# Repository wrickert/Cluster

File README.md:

# Cluster
Replacment cluster for GL1200 motorcycle. This is an early prototype to test how signals work. Main uC is Stm32f411re, will be running freertos. <br>

# Updates
1April - ordered v1 prototype<br>

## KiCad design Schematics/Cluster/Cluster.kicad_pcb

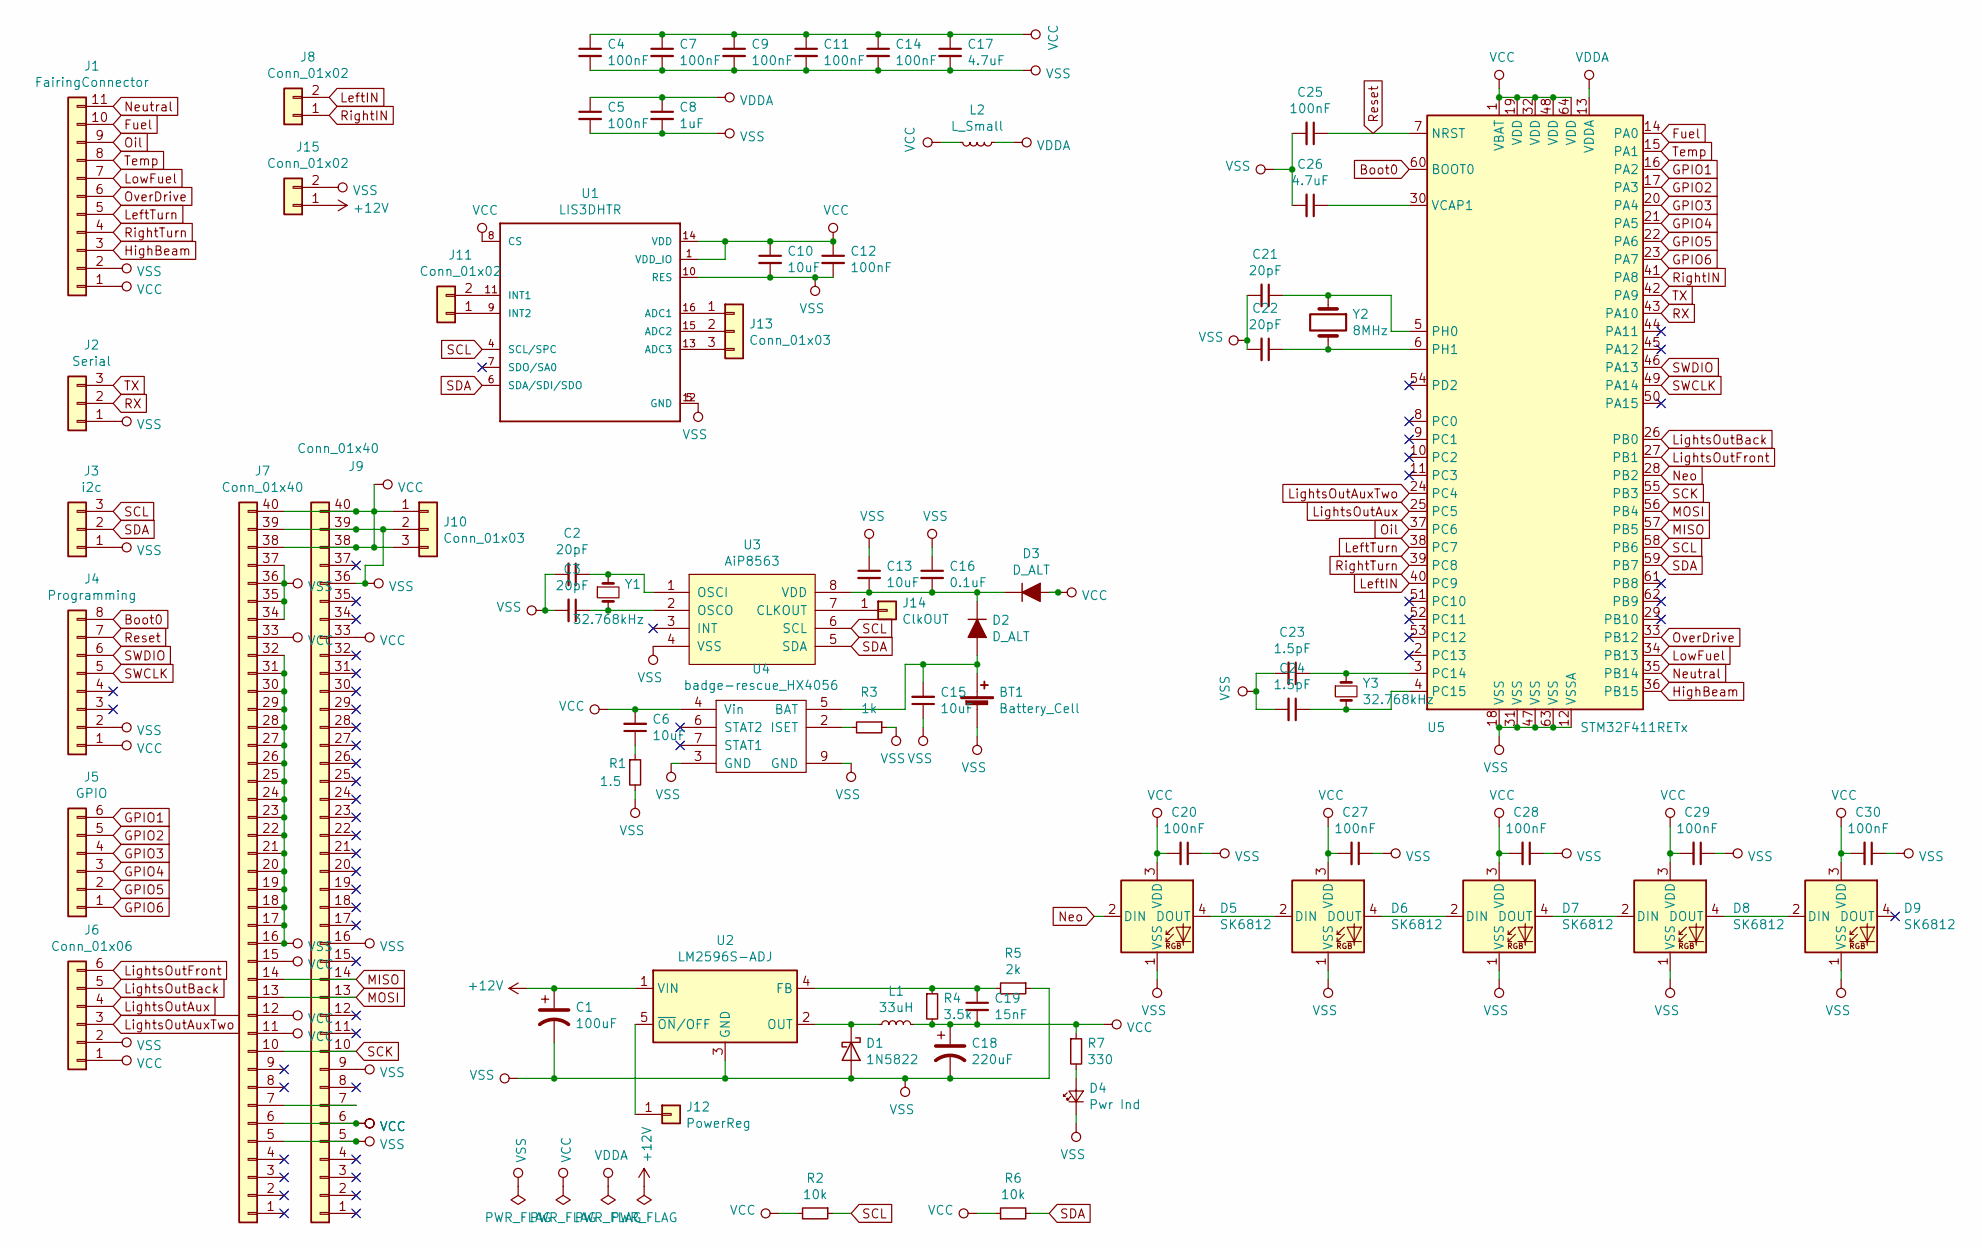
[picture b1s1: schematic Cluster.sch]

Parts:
BT1: Battery_Cell; Keystone_3008_1x2450-CoinCell
C1: 100uF; CP_Elec_8x10.5
C2, C3, C21, C22: 20pF; C_0805_2012Metric
C4, C5, C7, C9, C11, C12, C14, C20, C25, C27, C28, C29, C30: 100nF; C_0805_2012Metric
C6, C10, C13, C15: 10uF; C_0805_2012Metric
C8: 1uF; C_0805_2012Metric
C16: 0.1uF; C_0805_2012Metric
C17, C26: 4.7uF; C_0805_2012Metric
C18: 220uF; CP_Elec_8x10.5
C19: 15nF; C_0805_2012Metric
C23, C24: 1.5pF; C_0805_2012Metric
D1: 1N5822; D_SMA
D2, D3: D_ALT; D_0603
D4: Pwr Ind; LED_0603_1608Metric
D5, D6, D7, D8, D9: SK6812; LED_WS2812B-PLCC4
J1: FairingConnector; TerminalBlock_RND_205-00021_1x11_P5.00mm_Horizontal
J2: Serial; PinHeader_1x03_P2.54mm_Vertical
J3: i2c; PinHeader_1x03_P2.54mm_Vertical
J4: Programming; PinHeader_1x08_P2.54mm_Vertical
J5: GPIO; PinHeader_1x06_P2.54mm_Vertical
J6: Conn_01x06; PinHeader_1x06_P2.54mm_Vertical
J7: Conn_01x40; XF2M-4015
J8: Conn_01x02; TerminalBlock_RND_205-00001_Pitch5.00mm
J9: Conn_01x40; PinHeader_1x40_P1.00mm_Vertical
J10, J13: Conn_01x03; PinHeader_1x03_P2.54mm_Vertical
J11: Conn_01x02; PinHeader_1x02_P2.54mm_Vertical
J12: PowerReg; PinHeader_1x01_P2.54mm_Vertical
J14: ClkOUT; PinHeader_1x01_P2.54mm_Vertical
J15: Conn_01x02; TerminalBlock_RND_205-00012_1x02_P5.00mm_Horizontal
L1: 33uH; L_6.3x6.3_H3
L2: L_Small; L_0603_1608Metric
R1: 1.5; R_0805
R2, R6: 10k; R_0805
R3: 1k; R_0805
R4: 3.5k; R_0805
R5: 2k; R_0805
R7: 330; R_0603_1608Metric
U1: LIS3DHTR; LGA16R50P5X3_300X300X100N
U2: LM2596S-ADJ; TO-263-5_TabPin3
U3: AiP8563; MSOP-8_3x3mm_Pitch0.65mm
U4: badge-rescue_HX4056; HX4056
U5: STM32F411RETx; LQFP-64_10x10mm_Pitch0.5mm
Y1: 32.768kHz; Crystal_SMD_3215-2pin_3.2x1.5mm
Y2: 8MHz; Crystal_SMD_5032-2pin_5.0x3.2mm
Y3: 32.768kHz; Crystal_SMD_2012-2Pin_2.0x1.2mm

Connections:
+12V: C1.1, J15.1, U2.1 (VIN)
Boot0: J4.8, U5.60 (BOOT0)
Fuel: J1.10, U5.14 (PA0)
GPIO1: J5.6, U5.16 (PA2)
GPIO2: J5.5, U5.17 (PA3)
GPIO3: J5.4, U5.20 (PA4)
GPIO4: J5.3, U5.21 (PA5)
GPIO5: J5.2, U5.22 (PA6)
GPIO6: J5.1, U5.23 (PA7)
HighBeam: J1.3, U5.36 (PB15)
LeftIN: J8.2, U5.40 (PC9)
LeftTurn: J1.5, U5.38 (PC7)
LightsOutAux: J6.4, U5.25 (PC5)
LightsOutAuxTwo: J6.3, U5.24 (PC4)
LightsOutBack: J6.5, U5.26 (PB0)
LightsOutFront: J6.6, U5.27 (PB1)
LowFuel: J1.7, U5.34 (PB13)
MISO: J7.14, J9.14, U5.57 (PB5)
MOSI: J7.13, J9.13, U5.56 (PB4)
Neo: D5.2 (DIN), U5.28 (PB2)
unnamed: BT1.1 (+), C15.2, D2.2 (A), U4.5 (BAT)
unnamed: C2.1, U3.1 (OSCI), Y1.1
unnamed: C3.1, U3.2 (OSCO), Y1.2
unnamed: C6.1, R1.1
unnamed: C13.2, C16.2, D2.1 (K), D3.1 (K), U3.8 (VDD)
unnamed: C19.1, R4.1, R5.2, U2.4 (FB)
unnamed: C21.1, U5.5 (PH0), Y2.1
unnamed: C22.1, U5.6 (PH1), Y2.2
unnamed: C23.1, U5.3 (PC14), Y3.1
unnamed: C24.1, U5.4 (PC15), Y3.2
unnamed: C26.1, U5.30 (VCAP1)
unnamed: D1.1 (K), L1.1, U2.2 (OUT)
unnamed: D4.2 (A), R7.2
unnamed: D5.4 (DOUT), D6.2 (DIN)
unnamed: D6.4 (DOUT), D7.2 (DIN)
unnamed: D7.4 (DOUT), D8.2 (DIN)
unnamed: D8.4 (DOUT), D9.2 (DIN)
unnamed: J7.7, J9.7
unnamed: J11.1, U1.9 (INT2)
unnamed: J11.2, U1.11 (INT1)
unnamed: J12.1, U2.5 (~ON~/OFF)
unnamed: J13.1, U1.16 (ADC1)
unnamed: J13.2, U1.15 (ADC2)
unnamed: J13.3, U1.13 (ADC3)
unnamed: J14.1, U3.7 (CLKOUT)
unnamed: R3.2, U4.2 (ISET)
Neutral: J1.11, U5.35 (PB14)
Oil: J1.9, U5.37 (PC6)
OverDrive: J1.6, U5.33 (PB12)
RX: J2.2, U5.43 (PA10)
Reset: C25.1, J4.7, U5.7 (NRST)
RightIN: J8.1, U5.41 (PA8)
RightTurn: J1.4, U5.39 (PC8)
SCK: J7.10, J9.10, U5.55 (PB3)
SCL: J3.3, R2.1, U1.4 (SCL/SPC), U3.6 (SCL), U5.58 (PB6)
SDA: J3.2, R6.2, U1.6 (SDA/SDI/SDO), U3.5 (SDA), U5.59 (PB7)
SWCLK: J4.5, U5.49 (PA14)
SWDIO: J4.6, U5.46 (PA13)
TX: J2.3, U5.42 (PA9)
Temp: J1.8, U5.15 (PA1)
VCC: C4.1, C6.2, C7.1, C9.1, C10.1, C11.1, C12.1, C14.1, C17.1, C18.1, C19.2, C20.2, C27.2, C28.2, C29.2, C30.2, D3.2 (A), D5.3 (VDD), D6.3 (VDD), D7.3 (VDD), D8.3 (VDD), D9.3 (VDD), J1.1, J4.1, J6.1, J7.6, J7.11, J7.12, J7.15, J7.33, J7.38, J7.40, J9.6, J9.33, J9.38, J9.40, J10.1, J10.3, L1.2, L2.2, R2.2, R4.2, R6.1, R7.1, U1.1 (VDD_IO), U1.8 (CS), U1.14 (VDD), U4.4 (Vin), U5.1 (VBAT), U5.19 (VDD), U5.32 (VDD), U5.48 (VDD), U5.64 (VDD)
VDDA: C5.1, C8.1, L2.1, U5.13 (VDDA)
VSS: BT1.2 (-), C1.2, C2.2, C3.2, C4.2, C5.2, C7.2, C8.2, C9.2, C10.2, C11.2, C12.2, C13.1, C14.2, C15.1, C16.1, C17.2, C18.2, C20.1, C21.2, C22.2, C23.2, C24.2, C25.2, C26.2, C27.1, C28.1, C29.1, C30.1, D1.2 (A), D4.1 (K), D5.1 (VSS), D6.1 (VSS), D7.1 (VSS), D8.1 (VSS), D9.1 (VSS), J1.2, J2.1, J3.1, J4.2, J6.2, J7.5, J7.16, J7.17, J7.18, J7.19, J7.20, J7.21, J7.22, J7.23, J7.24, J7.25, J7.26, J7.27, J7.28, J7.29, J7.30, J7.31, J7.32, J7.34, J7.35, J7.36, J7.37, J7.39, J9.5, J9.9, J9.16, J9.36, J9.39, J10.2, J15.2, R1.2, R3.1, R5.1, U1.5 (GND), U1.10 (RES), U1.12 (GND), U2.3 (GND), U3.4 (VSS), U4.3 (GND), U4.9 (GND), U5.12 (VSSA), U5.18 (VSS), U5.31 (VSS), U5.47 (VSS), U5.63 (VSS)

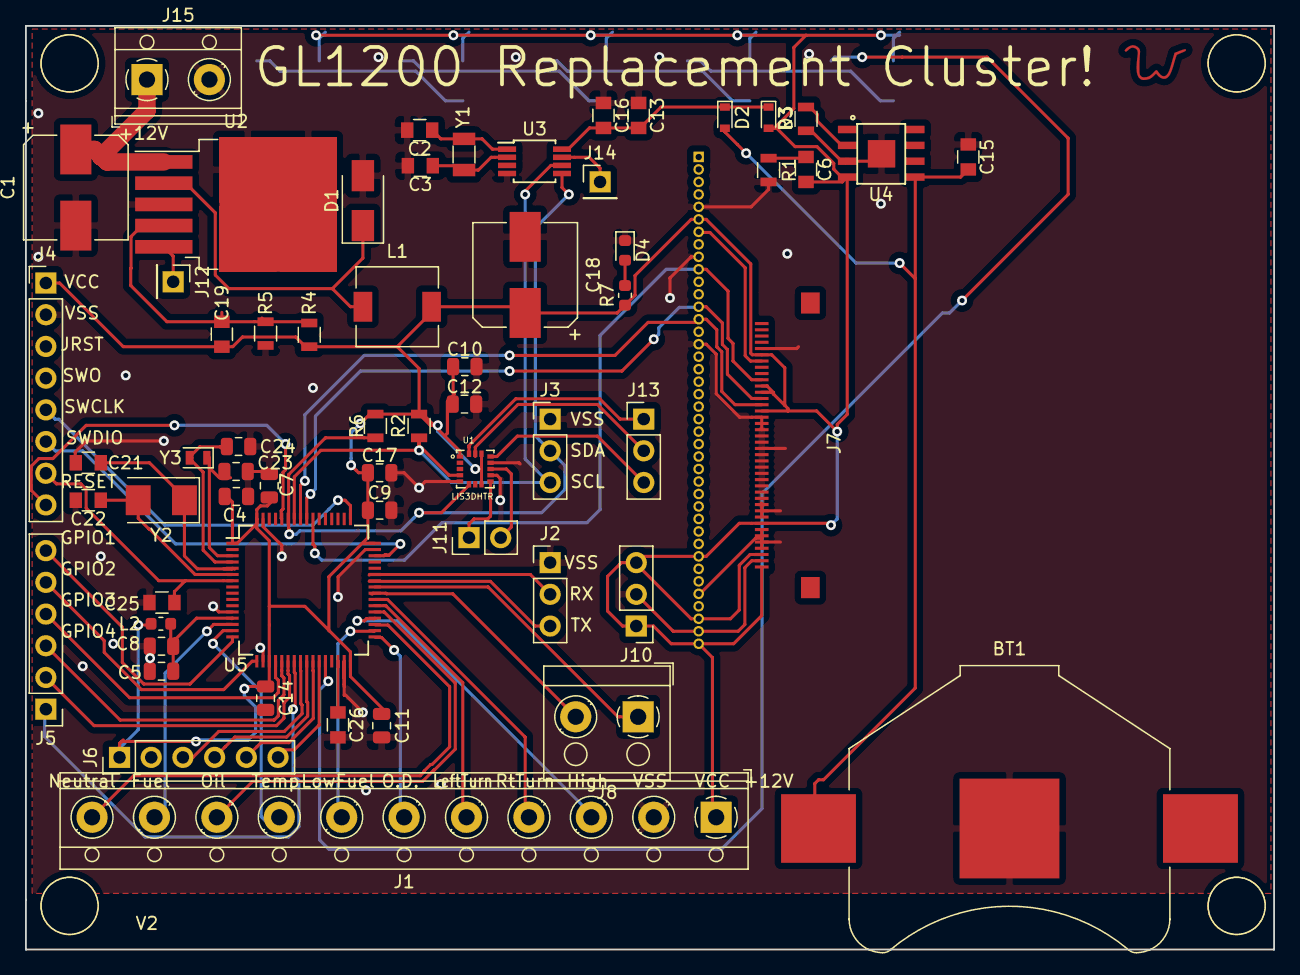
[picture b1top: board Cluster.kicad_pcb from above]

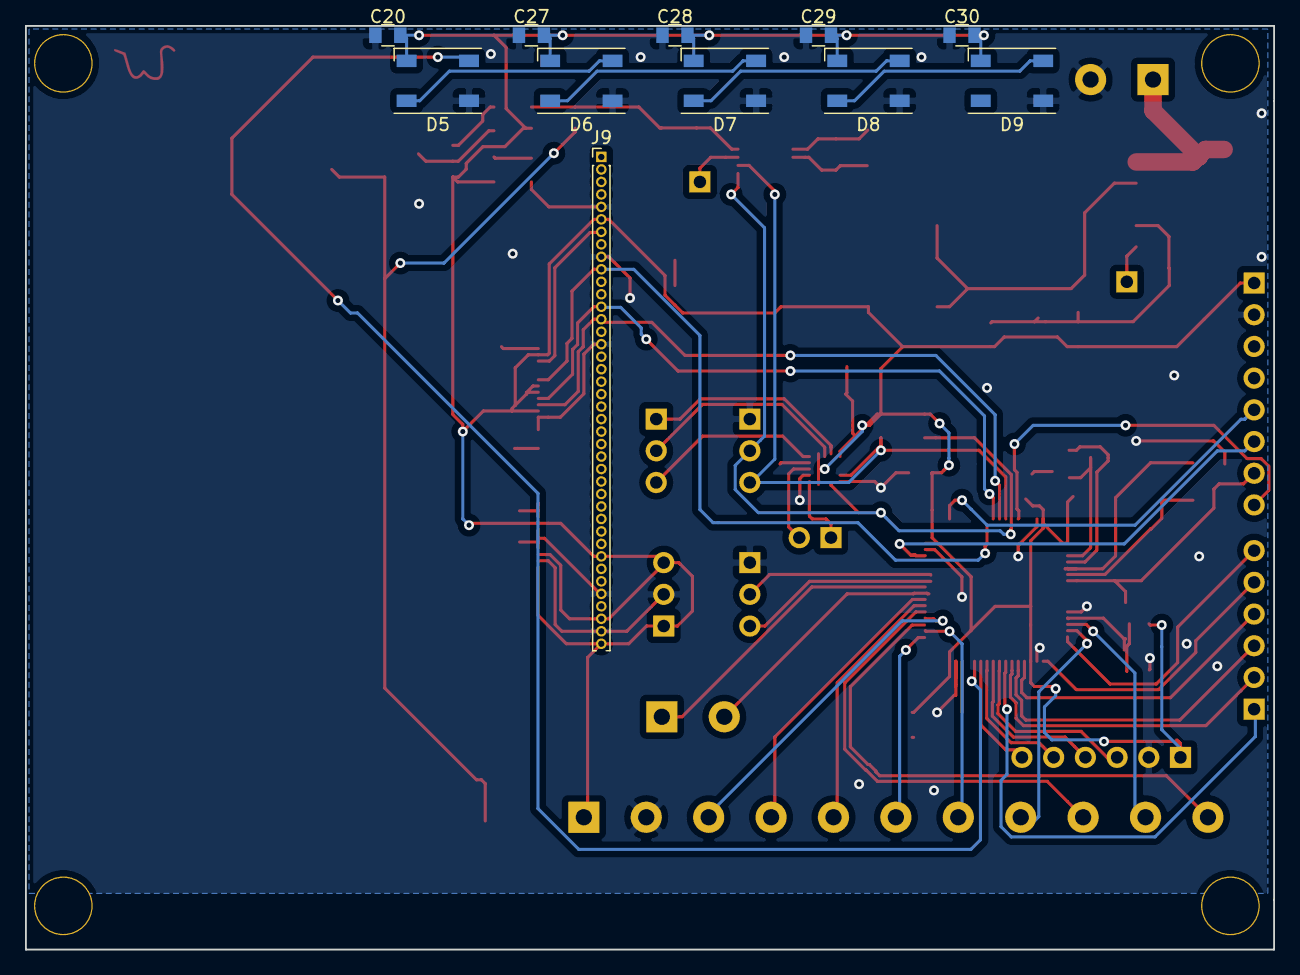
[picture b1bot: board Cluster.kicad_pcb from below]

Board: 2 copper layers, 100.0 x 74.0 mm, 73 parts (11 on the bottom side), 63 nets.

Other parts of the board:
Ref**: Val**; W

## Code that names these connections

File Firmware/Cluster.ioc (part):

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Mcu.Name=STM32F411R(C-E)Tx
Mcu.Package=LQFP64
Mcu.UserName=STM32F411RETx
PA0-WKUP.Signal=ADCx_IN0
PA1.Signal=ADCx_IN1
PA10.Signal=USART1_RX
PA2.Signal=ADCx_IN2
PA3.Signal=ADCx_IN3
PA4.Signal=GPIO_Input
PA6.Signal=GPIO_Input
PA7.Signal=GPIO_Input
PA9.Signal=USART1_TX
PB1.Signal=S_TIM3_CH4
PB14.Mode=Full_Duplex_Master
PB14.Signal=SPI2_MISO
PB15.Mode=Full_Duplex_Master
PB15.Signal=SPI2_MOSI
PB2.GPIOParameters=GPIO_Label
PB2.GPIO_Label=WS2812B
PB2.Signal=GPIO_Output
PB6.Mode=I2C
PB6.Signal=I2C1_SCL
PB7.Mode=I2C
PB7.Signal=I2C1_SDA
PC0.Signal=GPIO_Output
PC1.Signal=GPIO_Output
PC6.Signal=GPIO_Input
PC7.Mode=Full_Duplex_Master
PC7.Signal=SPI2_SCK
PC8.Signal=GPIO_Input
PH0\ -\ OSC_IN.Signal=RCC_OSC_IN
PH1\ -\ OSC_OUT.Signal=RCC_OSC_OUT
RCC.HSE_VALUE=25000000
RCC.SYSCLKFreq_VALUE=16000000
board=custom

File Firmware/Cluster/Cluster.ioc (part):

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Mcu.Name=STM32F411R(C-E)Tx
Mcu.Package=LQFP64
Mcu.UserName=STM32F411RETx
PA0-WKUP.Signal=ADCx_IN0
PA1.Signal=ADCx_IN1
PA10.Mode=Asynchronous
PA10.Signal=USART1_RX
PA2.Signal=ADCx_IN2
PA3.Signal=ADCx_IN3
PA9.Mode=Asynchronous
PA9.Signal=USART1_TX
PB12.Signal=GPIO_Input
PB13.Signal=GPIO_Input
PB14.Signal=GPIO_Input
PB15.Signal=GPIO_Input
PB6.Mode=I2C
PB6.Signal=I2C1_SCL
PB7.Mode=I2C
PB7.Signal=I2C1_SDA
PC6.Signal=GPIO_Input
PC7.Signal=GPIO_Input
PC8.Signal=GPIO_Input
PH0\ -\ OSC_IN.Signal=RCC_OSC_IN
PH1\ -\ OSC_OUT.Signal=RCC_OSC_OUT
RCC.HSE_VALUE=25000000
RCC.SYSCLKFreq_VALUE=16000000
board=custom

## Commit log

2019-04-02 PCB v1 ordered
2019-04-02 Added schematic screenshot
2019-04-02 Added missing time IC and turn signal inputs to schematic
2019-04-05 Finished design for turnsignal/taillight assembly
2019-04-23 Added stencil
2019-06-04 Ordered V2
2019-06-11 Why are there still ratsnest wires?
